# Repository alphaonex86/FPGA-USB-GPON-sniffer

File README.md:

# FPGA USB GPON sniffer

The cheapest in-line GPON dumper we could design: a USB device that sits in one ONU's drop fibre, regenerates
both directions and dumps that ONU's exchange with the OLT (activation PLOAM, BWmap, OMCI managed entities, low-rate
GEM traffic), every record tagged with its direction. Goal: diagnose and complete the open source Linux GPON stack.

Status: RTL and host tool written; the Artix-7 build meets timing and the whole chip, transceivers included, is
simulated (bursts regenerated bit for bit at a constant delay). Board routed (design rules clean). Nothing has been built or
measured.

## Why in-line and not a passive tap

A passive tap (the sniffer card of [FPGA-ONU-1GPON-1GE](https://github.com/alphaonex86/FPGA-ONU-1GPON-1GE)) takes about
4 dB from the ONU: it only fits homes that receive -23 dBm or better. This device receives each direction and emits
it again on the other side at the received level + 1 dB (floor -26 dBm, configurable), so the ONU and the OLT see
what they saw on the bare fibre.

## Block diagram

```
            OLT port (ONU-type optics)                              ONU port (OLT-type optics)
 OLT ====== RX 1490 nm --> CH0 RX --[ FIFO ]-----------> CH0 TX --> TX 1490 nm ==[ pad ]====== ONU
  fibre     TX 1310 nm <-- CH1 TX <--[ burst regen ]<--- CH1 RX <-- RX 1310 nm
                               |        Artix-7           |
                               +---> frame sync, filter <-+      155.52 MHz fixed oscillator
                                          records
                                             |
                                  USB3320 ULPI (USB 2.0 HS) ---- USB-C: power, dump
```

## Design

- 3R through the FPGA (re-amplify, re-shape, re-time). An analog burst repeater eats preamble bits (receiver
  settling, laser turn-on) the OLT needs; here the burst's head is rebuilt and the burst keeps its slot. The added
  latency is constant (about 100 ns each way): ranging absorbs it as 20 m of fibre.
- FPGA: AMD Artix-7 XC7A100T-2FGG484I, two GTP lanes: downstream duplex at 2488.32 Mb/s, upstream at 4976.64 Mb/s
  (4 samples per bit); Vivado.
- No VCXO: the downstream transmitter follows the received clock with the GTP's TX phase interpolator. The upstream
  receiver runs on the fixed oscillator and tracks the ONU's bit phase, so the bursts leave at a constant delay.
- Downstream bits pass unchanged (no FEC correction, no decryption): the ONU still does both.
- Upstream laser: on only while a burst arrives from the ONU, off at its last bit; dark with the FPGA unconfigured
  or hung (pull-ups and an independent maximum-burst cutoff).
- Dump: frame sync, FEC parity skip, GEM delineation and a filter (the ONU's Alloc-IDs and Port-IDs) in hardware;
  records of four kinds: PLOAM, BWmap entry, GEM fragment (downstream), burst (upstream). Low traffic is the target:
  records beyond what USB 2.0 high speed carries are lost under load, and counted.
- Dump rules ("Dump rules" below): a software-written match on each Ethernet frame's first 20 bytes decides what
  the USB carries of the user traffic, both directions. They work on the dump's copy only: the fibre relay and its
  bandwidth do not see them.
- USB: a USB3320 ULPI PHY and LUNA's serial device (CDC-ACM) in the FPGA: the record stream and the register writes
  on a plain /dev/ttyACM under Linux (no host library). Bitstream: a DIP-8 SPI flash in a socket, written in any
  programmer (`out/artix7/inline.bin`); no JTAG probe needed (the header's pads stay, unfitted, for rescue).
- Levels: both received powers measured, both lasers set by DAC; the fixed pad on the ONU port keeps the ONU's
  bursts under the receiver's overload. The host tool sets them ("Levels" below): without a host the lasers stay
  dark, and they keep their last levels when it leaves.
- Sensitivity: an APD receiver at the OLT port, for homes at -27 dBm and below. The dump does not correct FEC: on a
  link that only works thanks to FEC the ONU still does, the dump loses frames.

## Layout

- RTL, PCB generator and the host tool are shared with FPGA-ONU-1GPON-1GE, checked out next to this folder
  (`../FPGA-ONU-1GPON-1GE/common`).
- Host: `make -C ../FPGA-ONU-1GPON-1GE/common/sw/sniffer`, then `sniffer -i /dev/ttyACM0 -w dump.bin` (decoded
  records on stdout; `-r dump.bin` decodes a dump again; the port's raw bytes are such a dump).
- Here: `levels.example` (a unit's level file), `artix7/` (top level; `sh artix7/build.sh` builds the bitstream, `sh artix7/sim.sh` simulates the chip with
  the transceiver models), `pcb/inline/` (board, 84 x 54 mm; `lcsc.csv` parts list, `order-notes.md`; JLCPCB files:
  `python3 ../FPGA-ONU-1GPON-1GE/common/pcb/gen/fab.py inline`).

## Levels

`sniffer -i /dev/ttyACM0 -L unit.levels` sets the unit's levels from its level file (`levels.example`): lasers dark,
APD bias set and switched on, then every second each laser is aimed at what the other port receives + `gain_db`,
between `floor_dbm` and its `tx_max_dbm`. Starting with `-L` restarts both lasers from dark: the ONU activates again,
which is the exchange to dump. Without `-L` nothing is touched. Nothing is switched on when a DAC or the ADC does
not answer or when a current flows on the OLT port's APD lead before its bias is on; over 2 mA there later, bias and
lasers go off (VCC and APD leads exchanged on that BOSA, or a bias over the breakdown).

A unit's file is measured once, powers taken at the box's connectors with a power meter:

1. `olt_apd_v`, `onu_apd_v`: from each BOSA's test sheet. With only these two lines the tool prints the readings.
   `olt_rx_inverted = 1` when the OLT port has light and the downstream never synchronizes; `onu_rx_inverted = 1`
   (and the 5.1k offset resistor moved to `US_DIN_N`) when the ONU's bursts are never recognised: no BOSA datasheet
   says which lead of the TIA pair rises with light.
2. OLT port receiver: the drop fibre's power P on the meter, then the fibre on the port: `olt_rx_a_per_w` =
   printed APD mV / 1200 / P in mW.
3. ONU port laser (lit while the downstream is received): `onu_tx_bias_ma` at two values, `onu_tx_mod_ma = 0`, the
   meter on the ONU port: the two powers give `onu_tx_mw_per_ma` and `onu_tx_threshold_ma`, the printed monitor mV
   over the power `onu_tx_md_mv_per_mw`.
4. Bursts (a power meter does not read them, and the maximum-burst cutoff forbids a continuous upstream laser):
   `onu_rx_a_per_w` = printed APD mV / 1200 / the ONU's transmit power in mW (its ANI-G attribute, in the dump);
   the OLT port laser's threshold and slope from the BOSA's test sheet, corrected with the level the OLT reports
   for this ONU where it can be read.

## Dump rules

The ONU's user traffic can be more than USB 2.0 carries. Rules written by the host at each start choose which
Ethernet frames become records. A rule matches on the direction, the GEM Port-ID and the frame's first 20 bytes
(addresses, tags, ethertype) under a mask; the first rule that matches decides: `keep`, `drop` or `head` (the
frame's first `-S` bytes). `-F` is the action for the frames no rule matches (default `keep`). The device has 16
rules: the first is the tool's own (the OMCI Port-ID kept whole, both directions), 15 are for `-f`.

    sniffer -i /dev/ttyACM0 -F drop                            # PLOAM, BWmap, OMCI only: the MEs, whatever the load
    sniffer -i /dev/ttyACM0 -f keep,vlan=100 -F drop           # the same plus one VLAN (TR-069 management, ...)
    sniffer -i /dev/ttyACM0 -f drop,multicast                  # everything but multicast / broadcast
    sniffer -i /dev/ttyACM0 -F head -S 64                      # OMCI whole, 64 bytes of every other frame
    sniffer -i /dev/ttyACM0 -f drop,us,12=0800 -f drop,ds,port=1025,0=00112233/ffffff00

- Which Port-IDs: upstream, the ONU's bursts carry all of them. Downstream, the OMCI Port-ID (`Configure_Port-ID`
  or `-p`) always; with `-f`, `-F` or `-S` also the ONU's data Port-IDs, taken from the OMCI as the OLT creates them
  (GEM port network CTP), and those given by `-g ID`; a learned one is let go when the OLT deletes its CTP or resets
  the MIB. A tool started after the ONU was configured has not seen them: `-g`, or restart the ONU. Without rule
  options the downstream data is not dumped, as before.
- PLOAM, BWmap and OMCI records never pass the rules: an ME dump stays whole under any rule set. The records wait
  for the USB in 384 KB of the FPGA's block RAM, filled at twice the USB's rate: a peak is sent late instead of lost,
  about 10 ms of USB time. Only a load over the USB rate for longer loses records: counted, and
  printed.
- A frame split over several GEM fragments is judged on its first fragment, the others follow; a first fragment
  shorter than the bytes a rule compares does not match that rule.
- Both directions are judged at the line rate, before the record queues: a dropped frame costs nothing. Upstream, the
  GEM frames are found in the burst by their header check (the bytes before them, PLOAMu and DBRu, are not known to
  the FPGA): a frame taken out leaves its 5 header bytes, marked with the count of payload bytes left, so the decoder
  still walks the burst by its grants. A run of idle GEM headers (a granted allocation the ONU did not fill) is
  recorded as its last header with the count of the others: 5 bytes.
- Ciphered Port-IDs (most unicast, AES-128): the rules read such a frame through the key the ONU sent upstream
  (`Encryption_Key`, in clear), which the host gives to the FPGA at each `Key_Switching_Time`; the decoder deciphers
  the records the same way, the raw dump keeps the line's bytes. A host started after the key exchange has no key
  until the next one: such a frame is judged by the rules that compare no byte (`ds`, `port=N`), then by `-F`,
  counted in `UNREAD`, and printed as `ciphered` when kept. Excluding heavy traffic by Port-ID therefore works with or
  without the key; the upstream is never ciphered.
- The decoded text prints the `Encryption_Key` PLOAMu and deciphered frames: treat it like the raw dump, out of any
  public folder.
- Counters, printed when they change: fragments the rules dropped, ciphered frames judged unread, records lost.
- Design: registers, comparators and small memories only (one 32-bit masked compare per rule and clock, the rules
  in 16 x 5 words), so it carries over to an ASIC; the rule count and the bytes compared are generics.

## License

CERN-OHL-S-2.0.

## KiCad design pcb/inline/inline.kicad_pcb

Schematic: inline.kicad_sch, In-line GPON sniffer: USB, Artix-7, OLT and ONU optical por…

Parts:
C1, C90, C128, C150: 2.2u; C_0603_1608Metric
C2, C3, C4, C24, C25, C26, C27, C28, C29, C30, C31, C32, C33, C37, C38, C39, C40, C41, C43, C44, C45, C46, C47, C48, C49, C50, C51, C52, C53, C54, C55, C56, C60, C61, C62, C63, C65, C66, C67, C68, C70, C71, C73, C74, C75, C76, C77, C79, C80, C81, C82, C83, C84, C94, C95, C96, C97, C98, C99, C102, C103, C111, C113, C114, C115, C116, C117, C121, C122, C132, C133, C134, C135, C136, C139, C140, C145, C146, C148, C151: 100n; C_0402_1005Metric
C5, C20, C21, C22, C23: 1u; C_0402_1005Metric
C6, C8, C11, C14, C17, C34, C35, C42, C57, C58, C59, C64, C69, C72, C78, C85, C100, C101, C118, C123, C137, C138, C147, C149: 10u; C_0603_1608Metric
C7, C9, C10, C12, C13, C15, C16, C18, C19, C36: 22u; C_0805_2012Metric
C86, C87, C124, C125: 100n; C_0603_1608Metric; MPN 100 V X7R
C88, C126: 220p; C_0603_1608Metric; MPN 100 V X7R
C89, C127: 10n; C_0402_1005Metric; MPN 100 V X7R
C91, C92, C108, C129, C130: 10p; C_0402_1005Metric
C93, C112: 47p; C_0402_1005Metric
C104, C105, C106, C131, C141, C142, C143: 10n; C_0402_1005Metric
C107, C144: 27p; C_0402_1005Metric
C109: 1n; C_0402_1005Metric
C110: 100n; C_0603_1608Metric; MPN 100 nF 50 V X7R 0603
C119, C120: 220p; C_0402_1005Metric
D1: green; LED_0603_1608Metric; MPN green 0603
D2, D5: BAT46WJ; D_SOD-323F; MPN BAT46WJ (100 V)
D3, D4, D6, D7: 1N4148WS; D_SOD-323; MPN 1N4148WS
FB1, FB2, FB3, FB4, FB5, FB6, FB7, FB8, FB9: 120R@100MHz; L_0603_1608Metric; MPN BLM18PG121SN1D
H1, H2, H3, H4: M3; MountingHole_3.2mm_M3
J1: USB-C; USB_C_Receptacle_HRO_TYPE-C-31-M-12; MPN TYPE-C-31-M-12
J2: JTAG; PinHeader_1x06_P2.54mm_Vertical; not fitted
L1, L2, L3: 2.2u; L_Cenker_CKCS252012; MPN SLO252012F2R2MTT
L4, L6: 4.7u; L_Cenker_CKCS252012; MPN 4.7 uH, Isat >= 1 A, 2520
L5, L7: 10n; L_0402_1005Metric; MPN 10 nH 0402
R1, R2, R42, R44, R67, R75, R87, R88: 5.1k; R_0402_1005Metric
R3: 8.06k; R_0402_1005Metric; MPN 1 %
R4, R5, R20, R21, R22, R32, R38, R46, R47, R49, R50, R61, R80, R90, R91, R93, R94, R105: 10k; R_0402_1005Metric
R6: 453k; R_0402_1005Metric
R7, R8, R11: 100k; R_0402_1005Metric
R9: 150k; R_0402_1005Metric
R10: 200k; R_0402_1005Metric
R12: 100; R_0402_1005Metric; MPN 100 ohm 1 %
R13, R14, R16, R17, R18, R19, R28, R40, R64, R68, R106: 4.7k; R_0402_1005Metric
R15: 330; R_0402_1005Metric
R23, R30, R53, R60, R63, R78, R97: 1k; R_0402_1005Metric
R24, R25, R65, R66: 49.9; R_0402_1005Metric
R26: 7.5k; R_0402_1005Metric
R27: 2.4k; R_0402_1005Metric
R29, R41, R77, R86: 100; R_0402_1005Metric
R31: 300k; R_0603_1608Metric
R33, R81: 20k; R_0402_1005Metric
R34, R82: 39k; R_0402_1005Metric
R35, R59, R83, R103: 10; R_0402_1005Metric
R36, R84, R104: 1.5k; R_0402_1005Metric
R37, R85: 3.01k; R_0402_1005Metric
R39: 22k; R_0402_1005Metric
R43: 3k; R_0402_1005Metric
R45, R89: 9.1k; R_0402_1005Metric
R48, R92, R95: 1.8k; R_0402_1005Metric
R51: 2.7k; R_0402_1005Metric
R52, R96: 6.8k; R_0402_1005Metric
R54, R58, R98, R102: 15; R_0402_1005Metric
R55, R56, R99, R100: 5.6; R_0402_1005Metric
R57, R101: 75; R_0402_1005Metric
R62: 15k; R_0402_1005Metric
R69, R72: 180; R_0402_1005Metric
R70, R73: 124; R_0402_1005Metric
R71, R74: 150; R_0402_1005Metric
R76: 5.1k; R_0402_1005Metric; not fitted
R79: 330k; R_0603_1608Metric
R107, R108, R109: 2.2k; R_0402_1005Metric
SH1, SH2, SH3, SH4, SH5, SH6: ICSRC6508SFR; SHIELD_CLIP_6.5x0.8; MPN ICSRC6508SFR
U1: USBLC6-2SC6; SOT-23-6; MPN USBLC6-2SC6
U2: USB3320C-EZK-TR; QFN-32-1EP_5x5mm_P0.5mm_EP3.45x3.45mm_ThermalVias; MPN USB3320C-EZK-TR
U3, U4, U5: TLV62569DBVR; SOT-23-5; MPN TLV62569DBVR
U6: TLV74310PDBVR; SOT-23-5; MPN TLV74310PDBVR
U7: TLV74312PDBVR; SOT-23-5; MPN TLV74312PDBVR
U8: XC7A100T-2FGG484I; Xilinx_FGG484; MPN XC7A100T-2FGG484I
U9: W25Q32 DIP-8 in a socket; DIP-8_W7.62mm_Socket; MPN DS1001-01-08BT1NSF6X-JKB
U10: GPON ONU BOSA; BOSA_GPON; MPN GPON ONU BOSA, APD-TIA receiver (1310 n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
U11: SY88993AVKG; MSOP-10_3x3mm_P0.5mm; MPN SY88993AVKG
U12, U21: TPS61391RTER; WQFN-16-1EP_3x3mm_P0.5mm_EP1.68x1.68mm_ThermalVias; MPN TPS61391RTER
U13: SN74LVC1G07DBVR; SOT-23-5; MPN SN74LVC1G07DBVR
U14, U17: SN74LVC1G97DBVR; SOT-23-6; MPN SN74LVC1G97DBVR
U15, U23: MAX3643ETG+; TQFN-24-1EP_4x4mm_P0.5mm_EP2.6x2.6mm_ThermalVias; MPN MAX3643ETG+
U16: SN74LVC1G123DCUR; VSSOP-8_2.3x2mm_P0.5mm; MPN SN74LVC1G123DCUR
U18: SN74LVC1G32DBVR; SOT-23-5; MPN SN74LVC1G32DBVR
U19: GPON OLT BOSA; BOSA_GPON; MPN XL-BCB2111-LS-02
U20: SY88149NDLMG; QFN-16-1EP_3x3mm_P0.5mm_EP1.7x1.7mm_ThermalVias; MPN SY88149NDLMG
U22: TLV3501AIDBVR; SOT-23-6; MPN TLV3501AIDBVR
U24, U25: MCP4728T-E/UN; MSOP-10_3x3mm_P0.5mm; MPN MCP4728T-E/UN
U26: ADS7828E/2K5; TSSOP-16_4.4x5mm_P0.65mm; MPN ADS7828E/2K5
Y1: SX7DF155.520B20F30DNN; Oscillator_SMD_IDT_JU6-6_7.0x5.0mm_P2.54mm; MPN SX7DF155.520B20F30DNN

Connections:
+1V0: C15.1, C16.1, C24.1, C25.1, C26.1, C27.1, C28.1, C29.1, C30.1, C31.1, C32.1, C33.1, C34.1, C35.1, C36.1, L2.2, R8.1, U8.H8 (VCCINT), U8.H10 (VCCINT), U8.J7 (VCCINT), U8.J9 (VCCINT), U8.J11 (VCCBRAM), U8.K8 (VCCINT), U8.L7 (VCCINT), U8.L11 (VCCBRAM), U8.M8 (VCCINT), U8.N7 (VCCINT), U8.N11 (VCCBRAM), U8.P8 (VCCINT), U8.P10 (VCCINT), U8.R7 (VCCINT), U8.R9 (VCCINT), U8.T8 (VCCINT), U8.T10 (VCCINT)
+1V0_GT: C21.1, C60.1, C61.1, C62.1, C63.1, C64.1, U6.5 (OUT), U8.D6 (MGTAVCC), U8.D10 (MGTAVCC), U8.E8 (MGTAVCC), U8.F7 (MGTAVCC), U8.F9 (MGTAVCC)
+1V2_GT: C23.1, C65.1, C66.1, C67.1, C68.1, C69.1, R12.2, U7.5 (OUT), U8.B5 (MGTAVTT), U8.B7 (MGTAVTT), U8.B9 (MGTAVTT), U8.B11 (MGTAVTT), U8.C4 (MGTAVTT), U8.C8 (MGTAVTT)
+1V8: C18.1, C19.1, C20.1, C22.1, C37.1, C38.1, C39.1, C40.1, C41.1, C42.1, FB2.1, L3.2, R10.1, U6.1 (IN), U6.3 (EN), U7.1 (IN), U7.3 (EN), U8.H12 (VCCAUX), U8.K10 (VCCADC_0), U8.K12 (VCCAUX), U8.M12 (VCCAUX), U8.P12 (VCCAUX), U8.R11 (VCCAUX)
+1V8_USB: C3.1, C4.1, C5.1, FB2.2, U2.28 (VDD18), U2.30 (VDD18)
+3V3: C2.1, C8.1, C9.1, C10.1, C12.1, C13.1, C43.1, C44.1, C45.1, C46.1, C47.1, C48.1, C49.1, C50.1, C51.1, C52.1, C53.1, C54.1, C55.1, C56.1, C57.1, C58.1, C59.1, C70.1, C94.1, C95.1, C111.1, C113.1, C114.1, C132.1, C146.1, C147.1, C148.1, C149.1, C151.1, FB3.1, FB4.1, FB5.1, FB6.1, FB7.1, FB8.1, FB9.1, J2.1, L1.2, R6.1, R13.2, R14.2, R15.2, R16.2, R17.2, R18.2, R20.2, R21.2, R22.2, R28.2, R39.2, R62.2, R64.2, R68.2, R106.2, R107.2, R108.2, R109.2, U2.8 (REFSEL0), U2.11 (REFSEL1), U2.14 (REFSEL2), U2.32 (VDDIO), U8.A17 (VCCO_16), U8.AA7 (VCCO_34), U8.AA17 (VCCO_13), U8.AB4 (VCCO_34), U8.AB14 (VCCO_13), U8.B14 (VCCO_16), U8.C1 (VCCO_35), U8.C21 (VCCO_16), U8.D18 (VCCO_16), U8.E15 (VCCO_16), U8.F2 (VCCO_35), U8.F12 (VCCO_0), U8.F22 (VCCO_16), U8.G19 (VCCO_15), U8.H6 (VCCO_35), U8.H16 (VCCO_15), U8.J3 (VCCO_35), U8.J13 (VCCO_15), U8.K20 (VCCO_15), U8.L17 (VCCO_15), U8.M4 (VCCO_35), U8.M14 (VCCO_14), U8.N1 (VCCO_35), U8.N21 (VCCO_15), U8.P18 (VCCO_14), U8.R5 (VCCO_34), U8.R15 (VCCO_14), U8.T2 (VCCO_34), U8.T12 (VCCO_0), U8.T22 (VCCO_14), U8.U8 (CFGBVS_0), U8.U11 (M0_0), U8.U19 (VCCO_14), U8.U22 (IO_L3P_T0_DQS_PUDC_B_14), U8.V6 (VCCO_34), U8.V16 (VCCO_13), U8.W3 (VCCO_34), U8.W13 (VCCO_13), U8.Y10 (VCCO_13), U8.Y20 (VCCO_14), U9.8 (VCC), U13.5 (VCC), U14.5 (VCC), U16.3 (~CLR), U16.8 (VCC), U17.5 (VCC), U18.5 (VCC), U22.4 (V+), U24.1 (VDD), U25.1 (VDD), U26.16 (VDD)
+3V3_DS_APD: C84.1, C85.1, FB5.2, L4.1, R35.1, U12.10 (VIN)
+3V3_DS_APDA: C90.1, R35.2, U12.14 (AVCC), U12.15 (AVCC)
+3V3_DS_LD: C133.1, C134.1, C135.1, C136.1, C137.1, C138.1, D7.2 (A), FB9.2, L7.1, R87.2, R88.2, R98.1, U23.1 (VCCA), U23.4 (VCCS), U23.15 (VCCO), U23.18 (VCCO)
+3V3_DS_OPT: C75.1, C76.1, C77.1, C78.1, FB4.2, R26.2, U10.D (VCC), U11.10 (VCC)
+3V3_US_APD: C122.1, C123.1, FB8.2, L6.1, R83.1, U21.10 (VIN)
+3V3_US_APDA: C128.1, R83.2, U21.14 (AVCC), U21.15 (AVCC)
+3V3_US_LD: C96.1, C97.1, C98.1, C99.1, C100.1, C101.1, D4.2 (A), FB6.2, L5.1, R42.2, R44.2, R54.1, U15.1 (VCCA), U15.4 (VCCS), U15.15 (VCCO), U15.18 (VCCO)
+3V3_US_OPT: C115.1, C116.1, C117.1, C118.1, FB7.2, R67.2, U19.D (VCC), U20.5 (VCC), U20.16 (VCC)
+3V3_XO: C71.1, C72.1, FB3.2, Y1.1 (OE), Y1.6 (VDD)
+5V: C6.1, C7.1, C11.1, C14.1, C17.1, FB1.2, U2.21 (VBAT), U3.1 (EN), U3.4 (VIN), U4.1 (EN), U4.4 (VIN), U5.1 (EN), U5.4 (VIN)
ADC_REF: C150.1, U26.10 (REF)
APD_EN: R38.1, U8.A21 (IO_L21N_T3_DQS_16), U12.13 (EN), U21.13 (EN)
BEN_DLY: C112.1, R63.2, U17.1 (IN1)
BURST_CUT: U8.B21 (IO_L21P_T3_DQS_16), U17.4 (Y), U18.2
CCLK: U8.L12 (CCLK_0), U9.6 (CLK)
CUT_C: C110.1, U16.6 (Cext)
CUT_Q: U16.5 (Q), U17.6 (IN2)
CUT_RC: C110.2, R62.1, U16.7 (RCext)
DONE: R15.1, U8.G11 (DONE_0)
DS_APD_ADJ: R33.2, U24.6 (VOUTA)
DS_APD_CAP: C89.1, U12.9 (CAP)
DS_APD_FB: R31.2, R32.1, R33.1, U12.12 (FB)
DS_APD_ISHORT: R34.1, U12.11 (ISHORT)
DS_APD_MON: C91.1, R36.1, U12.4 (MON1), U26.1 (CH0)
DS_APD_MON2: C92.1, R37.1, U12.3 (MON2)
DS_DIN_N: C81.2, R25.1, U11.3 (/DIN)
DS_DIN_P: C79.2, R24.1, U11.2 (DIN)
DS_HV_APD: C88.1, U10.E (VAPD), U12.5 (APD)
DS_HV_FILT: C87.1, R29.2, R30.1
DS_HV_MONIN: R30.2, U12.6 (MONIN)
DS_HV_OUT: C86.1, D2.1 (K), R29.1, R31.1
DS_HV_SW: D2.2 (A), L4.2, U12.8 (SW)
DS_LASER_DIS: R106.1, U8.D22 (IO_L22N_T3_16), U23.8 (~EN)
DS_LA_N: C82.1, U11.8 (/DOUT)
DS_LA_P: C80.1, U11.9 (DOUT)
DS_LD_A: D6.2 (A), L7.2, R98.2, U19.T1 (LD_A)
DS_LD_BCMON: C143.1, R97.1, U23.9 (BCMON), U26.5 (CH4)
DS_LD_BEN_N: R88.1, R89.1, U23.6 (BEN-)
DS_LD_BEN_P: R87.1, U23.5 (BEN+)
DS_LD_BIASSET: R95.1, U23.24 (BIASSET)
DS_LD_BIAS_N: R103.1, U23.13 (BIAS-)
DS_LD_BIAS_N_D: D7.1 (K), R103.2
DS_LD_BIAS_P: R100.1, U23.14 (BIAS+)
DS_LD_BSET: R93.1, U25.8 (VOUTC)
DS_LD_COMP: C144.1, R101.2
DS_LD_IMAX: R96.1, U23.10 (IMAX)
DS_LD_IN_N: C140.2, R86.2, U23.3 (IN-)
DS_LD_IN_P: C139.2, R86.1, U23.2 (IN+)
DS_LD_K: R99.2, R100.2, R101.1, U19.T3 (LD_K)
DS_LD_MD: C145.1, R105.2, U26.4 (CH3)
DS_LD_MODSET: R92.1, U23.20 (MODSET)
DS_LD_MSET: R90.1, U25.9 (VOUTD)
DS_LD_OUT_N: R102.1, U23.17 (OUT-)
DS_LD_OUT_N_D: D6.1 (K), R102.2
DS_LD_OUT_P: R99.1, U23.16 (OUT+)
DS_LD_VBSET: C142.1, R93.2, R94.1, U23.23 (VBSET)
DS_LD_VMSET: C141.1, R90.2, R91.1, U23.21 (VMSET)
DS_LOS: R28.1, U8.E22 (IO_L22P_T3_16), U11.1 (/EN), U11.7 (LOS)
DS_LOSLVL: R26.1, R27.1, U11.5 (LOSLVL)
DS_MPD_A: R104.1, R105.1, U19.T2 (MPD_A)
DS_RX_N: C82.2, U8.A8 (MGTPRXN0_216)
DS_RX_P: C80.2, U8.B8 (MGTPRXP0_216)
DS_TIA_N: C81.1, U10.C (OUT-)
DS_TIA_P: C79.1, U10.A (OUT+)
DS_TX_N: C140.1, U8.A4 (MGTPTXN0_216)
DS_TX_P: C139.1, U8.B4 (MGTPTXP0_216)
DS_VREF: C83.1, R24.2, R25.2, R27.2, U11.4 (VREF)
FB_1V0: R8.2, R9.1, U4.5 (FB)
FB_1V8: R10.2, R11.1, U5.5 (FB)
FB_3V3: R6.2, R7.1, U3.5 (FB)
FLASH_CS: R16.1, U8.T19 (IO_L6P_T0_FCS_B_14), U9.1 (~CS)
FLASH_HOLD: R22.1, U9.7 (~HOLD/~RESET/IO_{3})
FLASH_WP: R21.1, U9.3 (~WP/IO_{2})
GND: C1.2, C2.2, C3.2, C4.2, C5.2, C6.2, C7.2, C8.2, C9.2, C10.2, C11.2, C12.2, C13.2, C14.2, C15.2, C16.2, C17.2, C18.2, C19.2, C20.2, C21.2, C22.2, C23.2, C24.2, C25.2, C26.2, C27.2, C28.2, C29.2, C30.2, C31.2, C32.2, C33.2, C34.2, C35.2, C36.2, C37.2, C38.2, C39.2, C40.2, C41.2, C42.2, C43.2, C44.2, C45.2, C46.2, C47.2, C48.2, C49.2, C50.2, C51.2, C52.2, C53.2, C54.2, C55.2, C56.2, C57.2, C58.2, C59.2, C60.2, C61.2, C62.2, C63.2, C64.2, C65.2, C66.2, C67.2, C68.2, C69.2, C70.2, C71.2, C72.2, C75.2, C76.2, C77.2, C78.2, C83.2, C84.2, C85.2, C86.2, C87.2, C88.2, C89.2, C90.2, C91.2, C92.2, C93.2, C94.2, C95.2, C96.2, C97.2, C98.2, C99.2, C100.2, C101.2, C104.2, C105.2, C106.2, C107.2, C108.2, C109.2, C111.2, C112.2, C113.2, C114.2, C115.2, C116.2, C117.2, C118.2, C121.2, C122.2, C123.2, C124.2, C125.2, C126.2, C127.2, C128.2, C129.2, C130.2, C131.2, C132.2, C133.2, C134.2, C135.2, C136.2, C137.2, C138.2, C141.2, C142.2, C143.2, C144.2, C145.2, C146.2, C147.2, C148.2, C149.2, C150.2, C151.2, J1.A1 (GND), J1.A12 (GND), J1.B1 (GND), J1.B12 (GND), J1.SH (SHIELD), J2.6, R1.2, R2.2, R3.2, R5.2, R7.2, R9.2, R11.2, R19.2, R23.2, R32.2, R34.2, R36.2, R37.2, R38.2, R40.2, R45.2, R47.2, R48.2, R50.2, R51.2, R52.2, R53.2, R60.2, R70.2, R71.2, R73.2, R74.2, R75.2, R76.2, R80.2, R82.2, R84.2, R85.2, R89.2, R91.2, R92.2, R94.2, R95.2, R96.2, R97.2, R104.2, SH1.1, SH2.1, SH3.1, SH4.1, SH5.1, SH6.1, U1.2 (GND), U2.33 (GND), U3.2 (GND), U4.2 (GND), U5.2 (GND), U6.2 (GND), U7.2 (GND), U8.A2 (GND), U8.A3 (GND), U8.A5 (GND), U8.A7 (GND), U8.A9 (GND), U8.A10 (MGTPRXN2_216), U8.A11 (GND), U8.A12 (GND), U8.A22 (GND), U8.AA2 (GND), U8.AA12 (GND), U8.AA22 (GND), U8.AB9 (GND), U8.AB19 (GND), U8.B3 (GND), U8.B10 (MGTPRXP2_216), U8.B12 (GND), U8.B19 (GND), U8.C3 (GND), U8.C6 (GND), U8.C9 (MGTPRXN3_216), U8.C10 (GND), U8.C12 (GND), U8.C16 (GND), U8.D3 (GND), U8.D4 (GND), U8.D8 (GND), U8.D9 (MGTPRXP3_216), U8.D12 (GND), U8.D13 (GND), U8.E4 (GND), U8.E5 (GND), U8.E7 (GND), U8.E9 (GND), U8.E11 (GND), U8.E12 (VCCBATT_0), U8.E20 (GND), U8.F5 (GND), U8.F11 (GND), U8.F17 (GND), U8.G5 (GND), U8.G6 (GND), U8.G7 (GND), U8.G8 (GND), U8.G9 (GND), U8.G10 (GND), U8.G12 (GND), U8.G14 (GND), U8.H1 (GND), U8.H7 (GND), U8.H9 (GND), U8.H11 (GND), U8.H21 (GND), U8.J8 (GND), U8.J10 (GND), U8.J12 (GND), U8.J18 (GND), U8.K5 (GND), U8.K7 (GND), U8.K9 (GNDADC_0), U8.K11 (GND), U8.K15 (GND), U8.L2 (GND), U8.L8 (GND), U8.L9 (VREFN_0), U8.L10 (VP_0), U8.L22 (GND), U8.M7 (GND), U8.M9 (VN_0), U8.M10 (VREFP_0), U8.M11 (GND), U8.M19 (GND), U8.N6 (GND), U8.N8 (GND), U8.N9 (DXN_0), U8.N10 (DXP_0), U8.N16 (GND), U8.P3 (GND), U8.P7 (GND), U8.P9 (GND), U8.P11 (GND), U8.P13 (GND), U8.R8 (GND), U8.R10 (GND), U8.R12 (GND), U8.R20 (GND), U8.T7 (GND), U8.T9 (GND), U8.T11 (GND), U8.T17 (GND), U8.U4 (GND), U8.U9 (M2_0), U8.U10 (M1_0), U8.U14 (GND), U8.V1 (GND), U8.V11 (GND), U8.V21 (GND), U8.W8 (GND), U8.W18 (GND), U8.Y5 (GND), U8.Y15 (GND), U9.4 (GND), U10.B (GND), U10.T4 (CASE), U11.6 (GND), U12.7 (GND), U12.16 (AGND), U12.17 (EP), U13.3 (GND), U14.2 (GND), U14.3 (IN0), U15.19 (GND), U15.25 (EP), U16.1 (~A), U16.4 (GND), U17.2 (GND), U17.3 (IN0), U18.3 (GND), U19.B (GND), U19.T4 (CASE), U20.3 (GND), U20.6 (RESET), U20.8 (GND), U20.10 (/AUTO_RESET), U20.11 (GND), U20.13 (LOS/SD_SEL), U20.17 (EP), U21.7 (GND), U21.16 (AGND), U21.17 (EP), U22.2 (V-), U22.6 (SHDN), U23.12 (MDIN), U23.19 (GND), U23.25 (EP), U24.4 (~LDAC), U24.10 (VSS), U25.4 (~LDAC), U25.10 (VSS), U26.6 (CH5), U26.7 (CH6), U26.8 (CH7), U26.9 (GND), U26.11 (COM), U26.12 (A0), U26.13 (A1), Y1.3 (GND)
GT_RREF: R12.1, U8.F8 (MGTRREF_216)
INIT_B: R14.1, U8.U12 (INIT_B_0)
LED_K: D1.1 (K), R23.1
LED_SYNC: D1.2 (A), U8.G21 (IO_L24P_T3_16)
MISO: R20.1, U8.R22 (IO_L1N_T0_D01_DIN_14), U9.2 (DO/IO_{1})
MOSI: U8.P22 (IO_L1P_T0_D00_MOSI_14), U9.5 (DI/IO_{0})
PROGRAM_B: R13.1, U8.N12 (PROGRAM_B_0)
REFCLK_N: C74.2, U8.E6 (MGTREFCLK0N_216)
REFCLK_P: C73.2, U8.F6 (MGTREFCLK0P_216)
SCL: R107.1, U8.D21 (IO_L23N_T3_16), U24.2 (SCL), U26.14 (SCL)
SCL2: R108.1, U8.E21 (IO_L23P_T3_16), U25.2 (SCL)
SDA: R109.1, U8.F21 (IO_25_16), U24.3 (SDA), U25.3 (SDA), U26.15 (SDA)
SW_1V0: L2.1, U4.3 (SW)
SW_1V8: L3.1, U5.3 (SW)
SW_3V3: L1.1, U3.3 (SW)
TCK: J2.2, R19.1, U8.V12 (TCK_0)
TDI: J2.3, R17.1, U8.R13 (TDI_0)
TDO: J2.4, U8.U13 (TDO_0)
TMS: J2.5, R18.1, U8.T13 (TMS_0)
ULPI_CLK: U2.1 (CLKOUT), U8.Y4 (IO_L11P_T1_SRCC_34)
ULPI_D0: U2.3 (DATA0), U8.AB1 (IO_L7N_T1_34)
ULPI_D1: U2.4 (DATA1), U8.AB2 (IO_L8N_T1_34)
ULPI_D2: U2.5 (DATA2), U8.AB3 (IO_L8P_T1_34)
ULPI_D3: U2.6 (DATA3), U8.AB5 (IO_L10N_T1_34)
ULPI_D4: U2.7 (DATA4), U8.AB6 (IO_L20N_T3_34)
ULPI_D5: U2.9 (DATA5), U8.AB7 (IO_L20P_T3_34)
ULPI_D6: U2.10 (DATA6), U8.AB8 (IO_L22N_T3_34)
ULPI_D7: U2.13 (DATA7), U8.AA1 (IO_L7P_T1_34)
ULPI_DIR: U2.31 (DIR), U8.AA3 (IO_L9N_T1_DQS_34)
ULPI_NXT: U2.2 (NXT), U8.AA4 (IO_L11N_T1_SRCC_34)
ULPI_REFCLK: U2.26 (REFCLK), U8.AA8 (IO_L22P_T3_34)
ULPI_RST_N: R5.1, U2.27 (RESETB), U8.AA6 (IO_L18N_T2_34)
ULPI_STP: U2.29 (STP), U8.AA5 (IO_L10P_T1_34)
USB_CC1: J1.A5 (CC1), R1.1
USB_CC2: J1.B5 (CC2), R2.1
USB_DM: J1.A7 (D-), J1.B7 (D-), U1.3 (I/O2), U1.4 (I/O2), U2.19 (DM)
USB_DP: J1.A6 (D+), J1.B6 (D+), U1.1 (I/O1), U1.6 (I/O1), U2.18 (DP)
USB_RBIAS: R3.1, U2.24 (RBIAS)
USB_VBUS_SENSE: R4.1, U2.22 (VBUS)
USB_VDD33: C1.1, U2.20 (VDD33), U2.23 (ID)
US_ABOVE: U8.G22 (IO_L24N_T3_16), U22.5
US_APD_ADJ: R81.2, U25.6 (VOUTA)
US_APD_CAP: C127.1, U21.9 (CAP)
US_APD_FB: R79.2, R80.1, R81.1, U21.12 (FB)
US_APD_ISHORT: R82.1, U21.11 (ISHORT)
US_APD_MON: C129.1, R84.1, U21.4 (MON1), U22.3 (+)
US_APD_MON2: C130.1, R85.1, U21.3 (MON2)
US_BEN: R40.1, U8.B22 (IO_L20N_T3_16), U14.1 (IN1)
US_DIN_N: C120.2, R66.1, R76.1, U20.4 (/DIN)
US_DIN_P: C119.2, R65.1, R75.1, U20.1 (DIN)
US_HV_APD: C126.1, U19.E (VAPD), U21.5 (APD)
US_HV_FILT: C125.1, R77.2, R78.1
US_HV_MONIN: R78.2, U21.6 (MONIN)
US_HV_OUT: C124.1, D5.1 (K), R77.1, R79.1
US_HV_SW: D5.2 (A), L6.2, U21.8 (SW)
US_LASER_DIS: R64.1, U8.C22 (IO_L20P_T3_16), U18.1
US_LA_N: R72.1, R74.1, U20.9 (/DOUT)
US_LA_P: R69.1, R71.1, U20.12 (DOUT)
US_LD_A: D3.2 (A), L5.2, R54.2, U10.T1 (LD_A)
US_LD_BCMON: C106.1, R53.1, U15.9 (BCMON), U26.3 (CH2)
US_LD_BEN: R43.1, R63.1, U14.4 (Y), U16.2 (B)
US_LD_BEN_N: R44.1, R45.1, U15.6 (BEN-)
US_LD_BEN_P: R42.1, R43.2, U15.5 (BEN+)
US_LD_BIASSET: R51.1, U15.24 (BIASSET)
US_LD_BIAS_N: R59.1, U15.13 (BIAS-)
US_LD_BIAS_N_D: D4.1 (K), R59.2
US_LD_BIAS_P: R56.1, U15.14 (BIAS+)
US_LD_BSET: R49.1, U24.7 (VOUTB)
US_LD_COMP: C107.1, R57.2
US_LD_DIS: U15.8 (~EN), U18.4
US_LD_IMAX: R52.1, U15.10 (IMAX)
US_LD_IN_N: C103.2, R41.2, U15.3 (IN-)
US_LD_IN_P: C102.2, R41.1, U15.2 (IN+)
US_LD_K: R55.2, R56.2, R57.1, U10.T3 (LD_K)
US_LD_MD: C109.1, R61.2, U26.2 (CH1)
US_LD_MDOUT: R61.1, U15.11 (MDOUT)
US_LD_MODSET: R48.1, U15.20 (MODSET)
US_LD_MSET: R46.1, U24.8 (VOUTC)
US_LD_OUT_N: R58.1, U15.17 (OUT-)
US_LD_OUT_N_D: D3.1 (K), R58.2
US_LD_OUT_P: R55.1, U15.16 (OUT+)
US_LD_VBSET: C105.1, R49.2, R50.1, U15.23 (VBSET)
US_LD_VMSET: C104.1, R46.2, R47.1, U15.21 (VMSET)
US_LOS: R68.1, U13.2, U20.7 (SD/LOS), U20.15 (JAM)
US_MPD_A: C108.1, R60.1, U10.T2 (MPD_A), U15.12 (MDIN)
US_QUIET: C93.1, R39.1, U13.4, U14.6 (IN2)
US_RSSI_REF: C131.1, U22.1 (-), U25.7 (VOUTB)
US_RX_N: R72.2, R73.1, U8.C11 (MGTPRXN1_216)
US_RX_P: R69.2, R70.1, U8.D11 (MGTPRXP1_216)
US_SDLVL: R67.1, U20.14 (LOS/SDLVL)
US_TIA_N: C120.1, U19.C (OUT-)
US_TIA_P: C119.1, U19.A (OUT+)
US_TX_N: C103.1, U8.C5 (MGTPTXN1_216)
US_TX_P: C102.1, U8.D5 (MGTPTXP1_216)
US_VREF: C121.1, R65.2, R66.2, U20.2 (VREF)
VBUS: FB1.1, J1.A4 (VBUS), J1.A9 (VBUS), J1.B4 (VBUS), J1.B9 (VBUS), R4.2, U1.5 (VBUS)
XO_OUT_N: C74.1, Y1.5 (OUT-)
XO_OUT_P: C73.1, Y1.4 (OUT+)

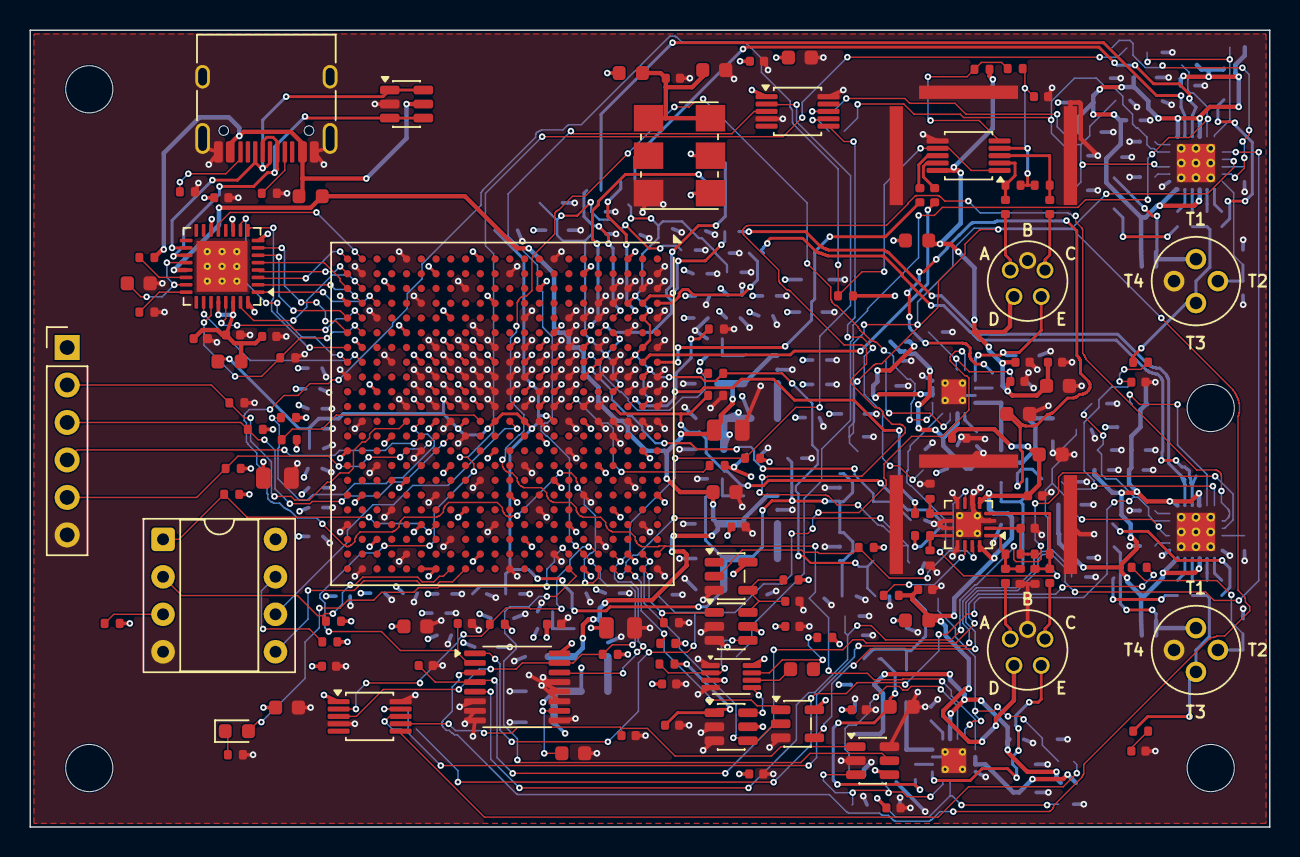
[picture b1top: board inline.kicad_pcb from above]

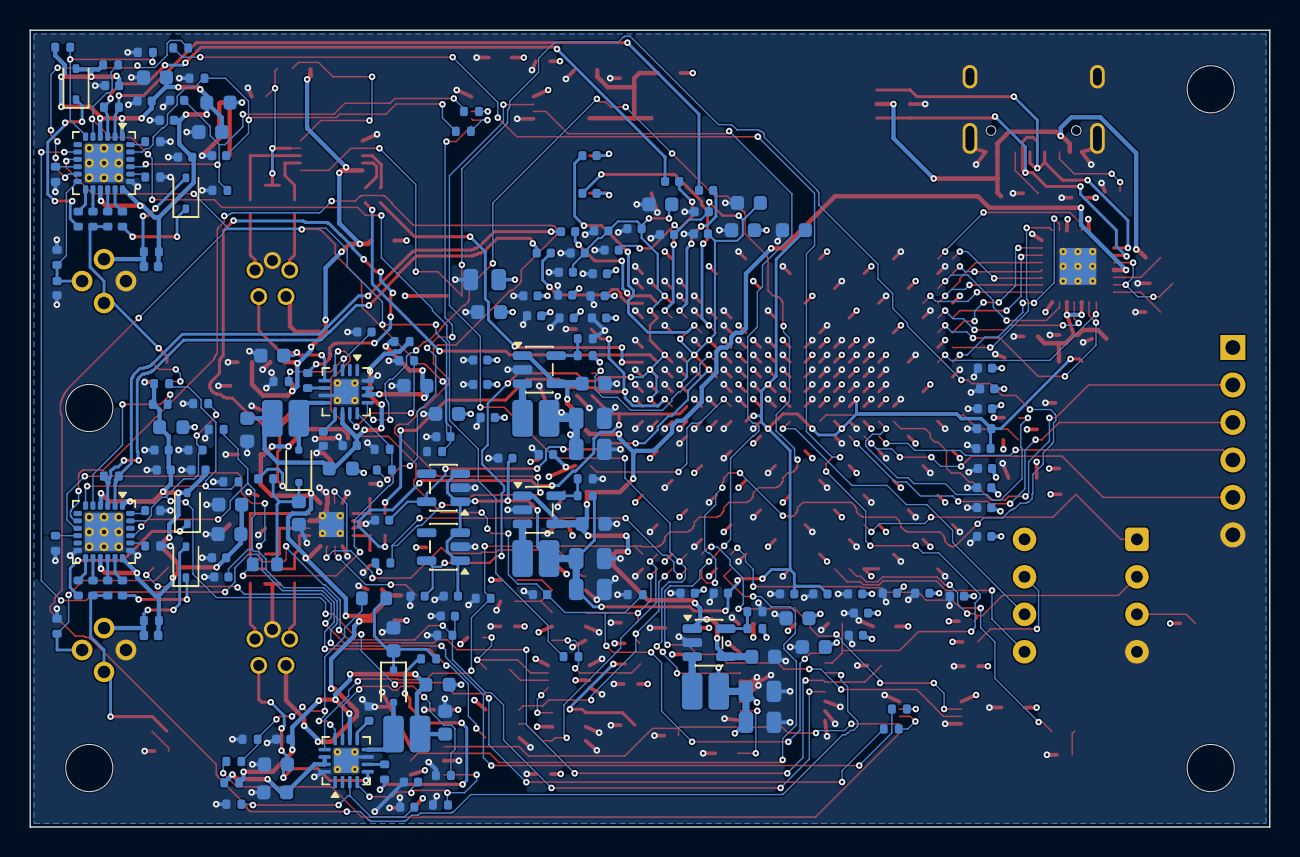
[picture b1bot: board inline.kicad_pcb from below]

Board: 4 copper layers, 84.0 x 54.0 mm, 322 parts (191 on the bottom side), 178 nets.

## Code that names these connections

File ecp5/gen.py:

#!/usr/bin/env python3
# SPDX-License-Identifier: CERN-OHL-S-2.0
"""Writes the ECP5 build inputs: dcu_params.vh (the sniffer card's DCU tables, both transmitters on) and inline.lpf
(the clocks, and every pin's ball read from the routed board when there is one).
Usage: gen.py <out dir> [board.kicad_pcb]"""
import os
import sys

sys.path.insert(0, os.path.join(os.path.dirname(os.path.abspath(__file__)), '../../FPGA-ONU-1GPON-1GE/sniffer/ecp5'))
import gen as card  # noqa: E402

SERDES = card.SERDES + ['DS_TX_P', 'DS_TX_N', 'US_TX_P', 'US_TX_N']  # dedicated pads: no IO type
PINS = (['DS_LOS', 'DS_LASER_DIS', 'US_LASER_DIS', 'US_BEN', 'US_ABOVE', 'VCXO_PWM', 'FT_RXF_N', 'FT_TXE_N', 'FT_RD_N', 'FT_WR_N', 'SCL', 'SDA',
         'LED_SYNC'] + [f'FT_D{i}' for i in range(8)])


def port(net):
    """Top-level port of a net: FT_D3 -> FT_D[3]."""
    return f'FT_D[{net[4:]}]' if net.startswith('FT_D') else net


def main(out, pcb=None):
    card.write_params(out, {0: card.TX_ON, 1: card.TX_ON})
    with open(f'{out}/inline.lpf', 'w') as f:
        if pcb:
            pins = card.board_pins(pcb, lambda net: net in PINS or net in SERDES)
            missing = [n for n in PINS + SERDES if n not in pins]
            if missing:
                sys.exit(f'{pcb}: no ECP5 ball for {missing}')
            for net in PINS:
                f.write(f'LOCATE COMP "{port(net)}" SITE "{pins[net]}";\nIOBUF PORT "{port(net)}" IO_TYPE=LVCMOS33;\n')
            for net in SERDES:
                f.write(f'LOCATE COMP "{net}" SITE "{pins[net]}";\n')
        else:  # fit only: the DDR output needs a ball, any left-bank one
            f.write('LOCATE COMP "US_BEN" SITE "C4";\nIOBUF PORT "US_BEN" IO_TYPE=LVCMOS33;\n')
        f.write('FREQUENCY NET "ref_clk" 124.416 MHZ;\nFREQUENCY NET "ds_clk" 124.416 MHZ;\n'
                'FREQUENCY NET "out_clk" 77.76 MHZ;\n')


if __name__ == '__main__':
    if len(sys.argv) not in (2, 3):
        sys.exit(__doc__)
    main(*sys.argv[1:])

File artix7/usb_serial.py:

# SPDX-License-Identifier: CERN-OHL-S-2.0
"""Writes usb_serial.v: LUNA's high-speed USB serial device (CDC-ACM, a /dev/ttyACM on the host) on a ULPI PHY in
output clock mode (USB3320). Its `usb` domain is the PHY's 60 MHz CLKOUT; `rst` high holds the PHY in reset (RESETB =
!ulpi_rst). Streams of bytes: rx from the host, tx to it; a tx byte with `last` ends its packet (sent at once).
Usage: python usb_serial.py OUT.v  (with amaranth and luna-usb, see build.sh)"""
import sys
from types import SimpleNamespace
from amaranth import ClockDomain, Elaboratable, Module, ResetSignal, Signal
from amaranth.back import verilog
from luna.full_devices import USBSerialDevice


def pins(**fields):
    return SimpleNamespace(**{k: Signal(w, name=f'{prefix}') for k, (prefix, w) in fields.items()})


class UsbSerial(Elaboratable):
    def __init__(self):
        self.ulpi = SimpleNamespace(
            data=pins(i=('ulpi_data_i', 8), o=('ulpi_data_o', 8), oe=('ulpi_data_oe', 1)),
            dir=pins(i=('ulpi_dir', 1)), nxt=pins(i=('ulpi_nxt', 1)), stp=pins(o=('ulpi_stp', 1)),
            rst=pins(o=('ulpi_rst', 1)), clk=pins(i=('ulpi_clk', 1)))   # the usb domain's clock: LUNA ties it
        for name, width in (('tx_data', 8), ('tx_valid', 1), ('tx_last', 1), ('tx_ready', 1), ('rx_data', 8), ('rx_valid', 1),
                            ('rx_ready', 1), ('rst', 1)):
            setattr(self, name, Signal(width, name=name))

    def elaborate(self, platform):
        m = Module()
        m.domains.usb = ClockDomain()
        m.d.comb += ResetSignal('usb').eq(self.rst)
        m.submodules.serial = serial = USBSerialDevice(bus=self.ulpi, idVendor=0x1209, idProduct=0x0001,
                                                       manufacturer_string='CatchChallenger',
                                                       product_string='GPON in-line sniffer', max_packet_size=512)
        m.d.comb += [
            serial.connect.eq(1),
            serial.tx.payload.eq(self.tx_data), serial.tx.valid.eq(self.tx_valid), serial.tx.last.eq(self.tx_last),
            self.tx_ready.eq(serial.tx.ready),
            self.rx_data.eq(serial.rx.payload), self.rx_valid.eq(serial.rx.valid), serial.rx.ready.eq(self.rx_ready),
        ]
        return m


if __name__ == '__main__':
    top = UsbSerial()
    u = top.ulpi
    ports = [u.clk.i, top.rst, u.data.i, u.data.o, u.data.oe, u.dir.i, u.nxt.i, u.stp.o, u.rst.o,
             top.tx_data, top.tx_valid, top.tx_last, top.tx_ready, top.rx_data, top.rx_valid, top.rx_ready]
    with open(sys.argv[1], 'w') as f:
        f.write(verilog.convert(top, name='usb_serial', ports=ports))
